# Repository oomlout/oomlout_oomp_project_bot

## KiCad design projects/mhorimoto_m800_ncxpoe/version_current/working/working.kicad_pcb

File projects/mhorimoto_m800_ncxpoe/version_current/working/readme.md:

# OOMP Project  
## M800-NCxPoE  by mhorimoto  
  
oomp key: oomp_projects_flat_mhorimoto_m800_ncxpoe  
(snippet of original readme)  
  
- NCxPoE  

  full source readme at [readme_src.md](readme_src.md)  
  
source repo at: [https://github.com/mhorimoto/M800-NCxPoE](https://github.com/mhorimoto/M800-NCxPoE)  
## Board  

## Schematic  

[schematic pdf](working_schematic.pdf)  
## Images

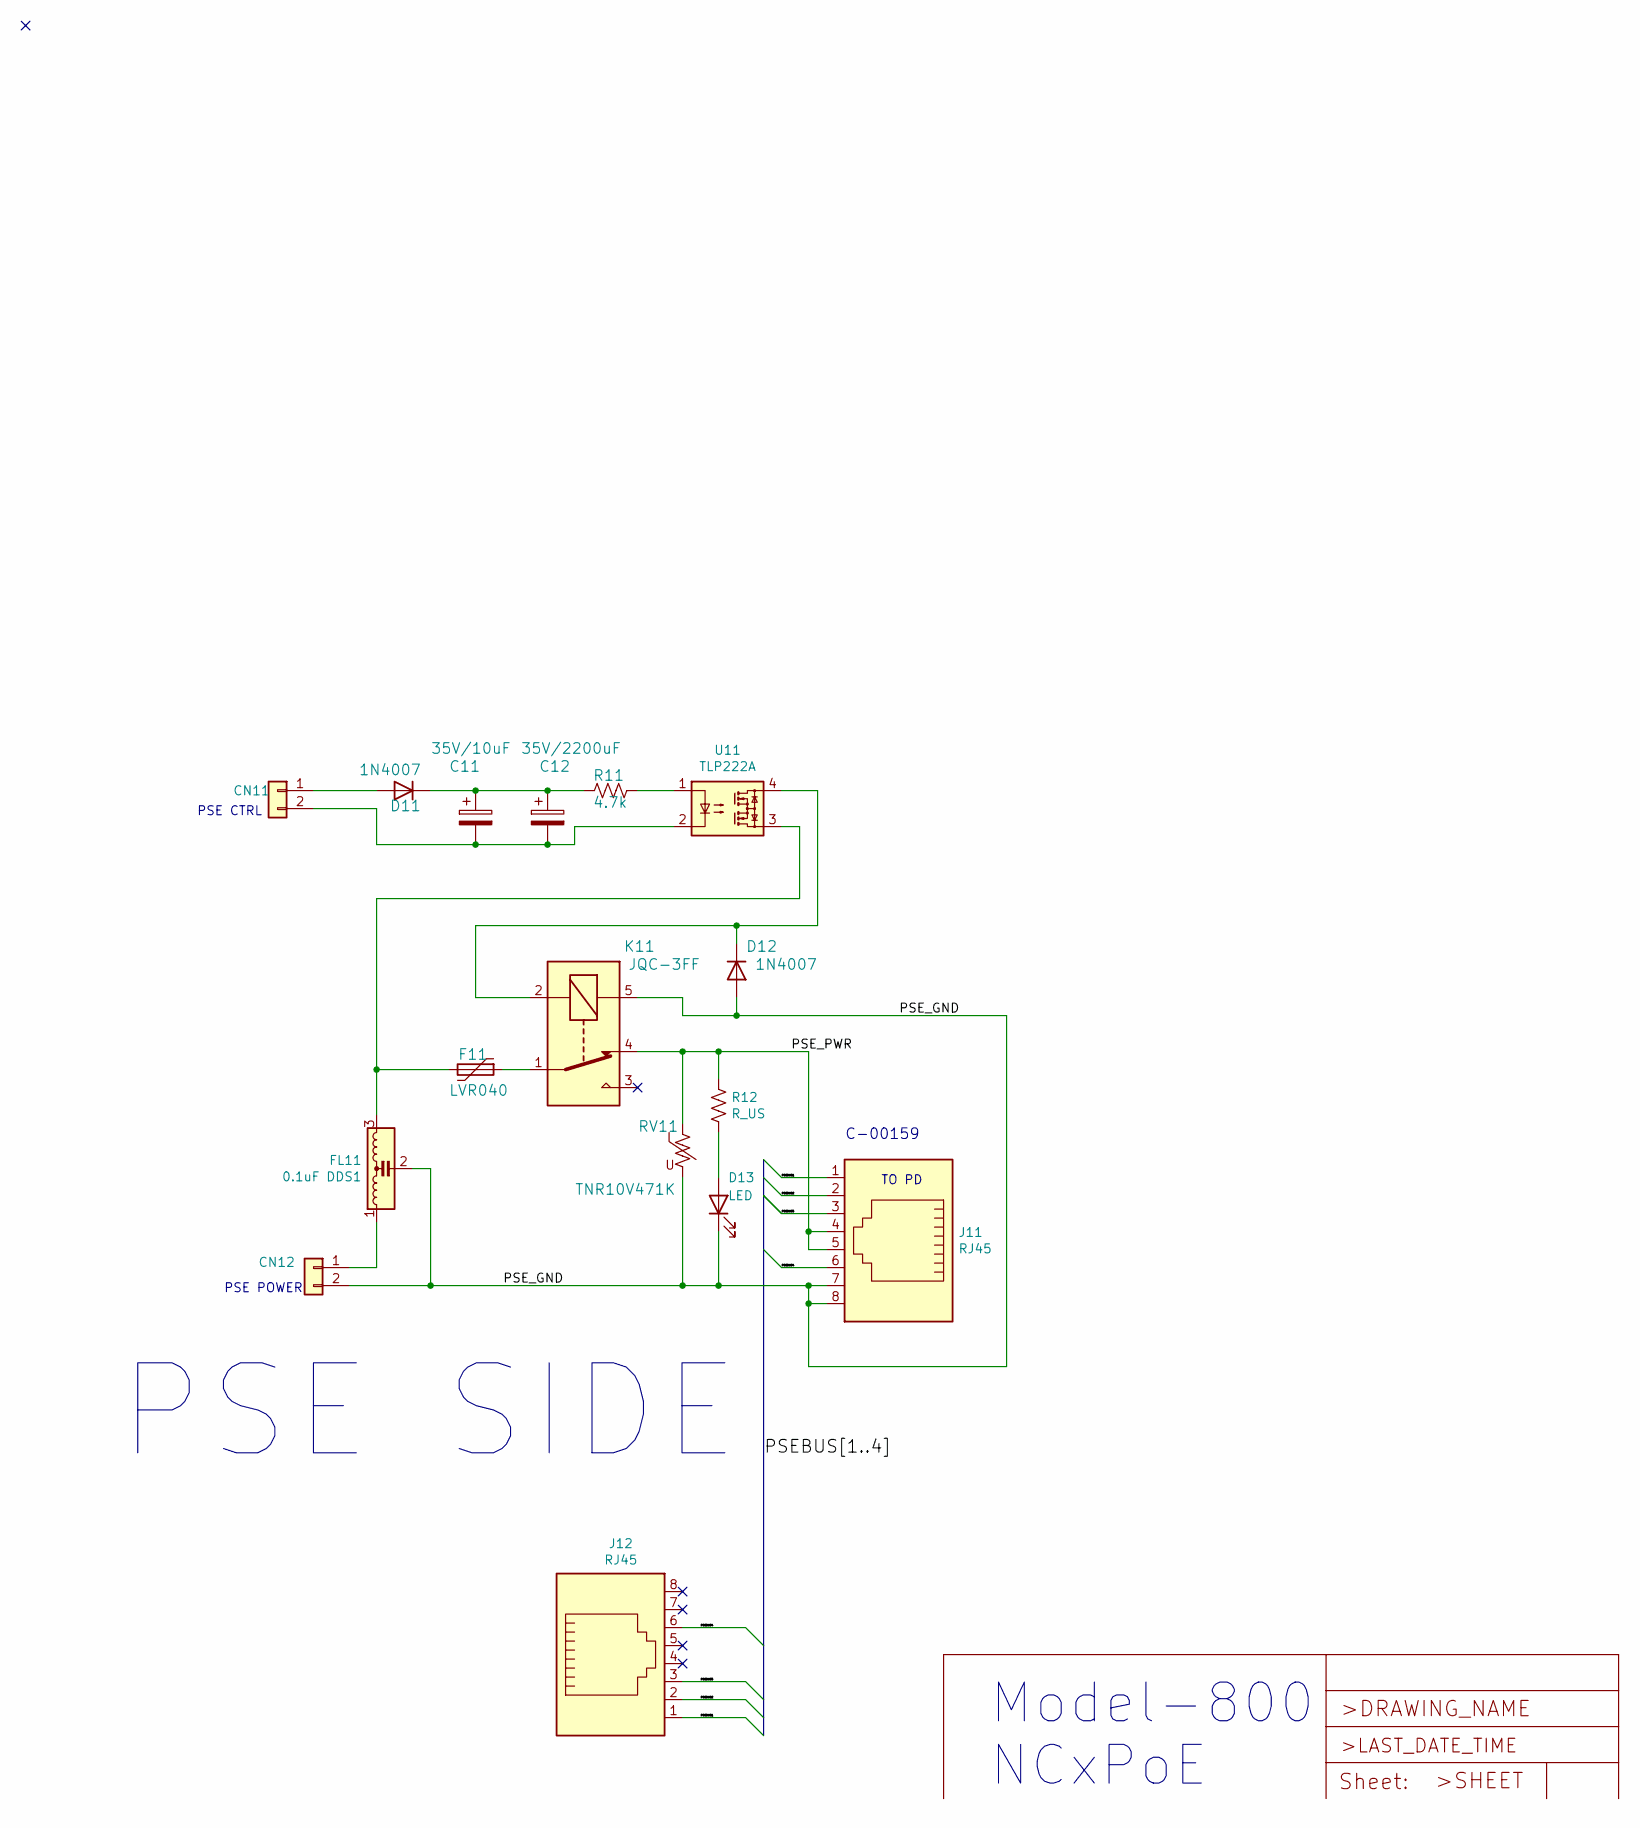
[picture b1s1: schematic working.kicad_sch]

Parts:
C11: 35V/10uF; C_Disc_D6.0mm_W2.5mm_P5.00mm
C12: 35V/2200uF; CP_Radial_D16.0mm_P7.50mm
CN11, CN12: 02-XH-A; JST_XH_B2B-XH-A_1x02_P2.50mm_Vertical
D11, D12: 1N4007; D_DO-41_SOD81_P10.16mm_Horizontal
D13: LED; LED_D3.0mm
F11: LVR040; Fuse_BelFuse_0ZRE0033FF_L11.4mm_W3.8mm
FL11: 0.1uF DDS1; DSS1
J11, J12: RJ45; RJ45_Neltron_7810-8P8C
K11: JQC-3FF; Relay_SPDT_Omron-G5LE-1
R11: 4.7k; R_Axial_DIN0207_L6.3mm_D2.5mm_P10.16mm_Horizontal
R12: R_US; R_Axial_DIN0207_L6.3mm_D2.5mm_P10.16mm_Horizontal
RV11: TNR10V471K; RV_Disc_D12mm_W3.9mm_P7.5mm
U11: TLP222A; DIP-4_W7.62mm

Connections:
/PSEBUS1: J11.1, J12.1
/PSEBUS2: J11.2, J12.2
/PSEBUS3: J11.3, J12.3
/PSEBUS4: J11.6, J12.6
/PSE_GND: CN12.2, D12.2 (A), D13.1 (K), FL11.2, J11.7, J11.8, K11.5, RV11.2
/PSE_PWR: J11.4, J11.5, K11.4, R12.1, RV11.1
unnamed: C11.1, C12.1, D11.1 (K), R11.2
unnamed: C11.2, C12.2, CN11.2, U11.2
unnamed: CN11.1, D11.2 (A)
unnamed: CN12.1, FL11.1
unnamed: D12.1 (K), K11.2, U11.4
unnamed: D13.2 (A), R12.2
unnamed: F11.1, K11.1
unnamed: F11.2, FL11.3, U11.3
unnamed: R11.1, U11.1

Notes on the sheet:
C-00159
PSE CTRL
TO PD
PSE POWER
PSE SIDE
Model-800 NCxPoE

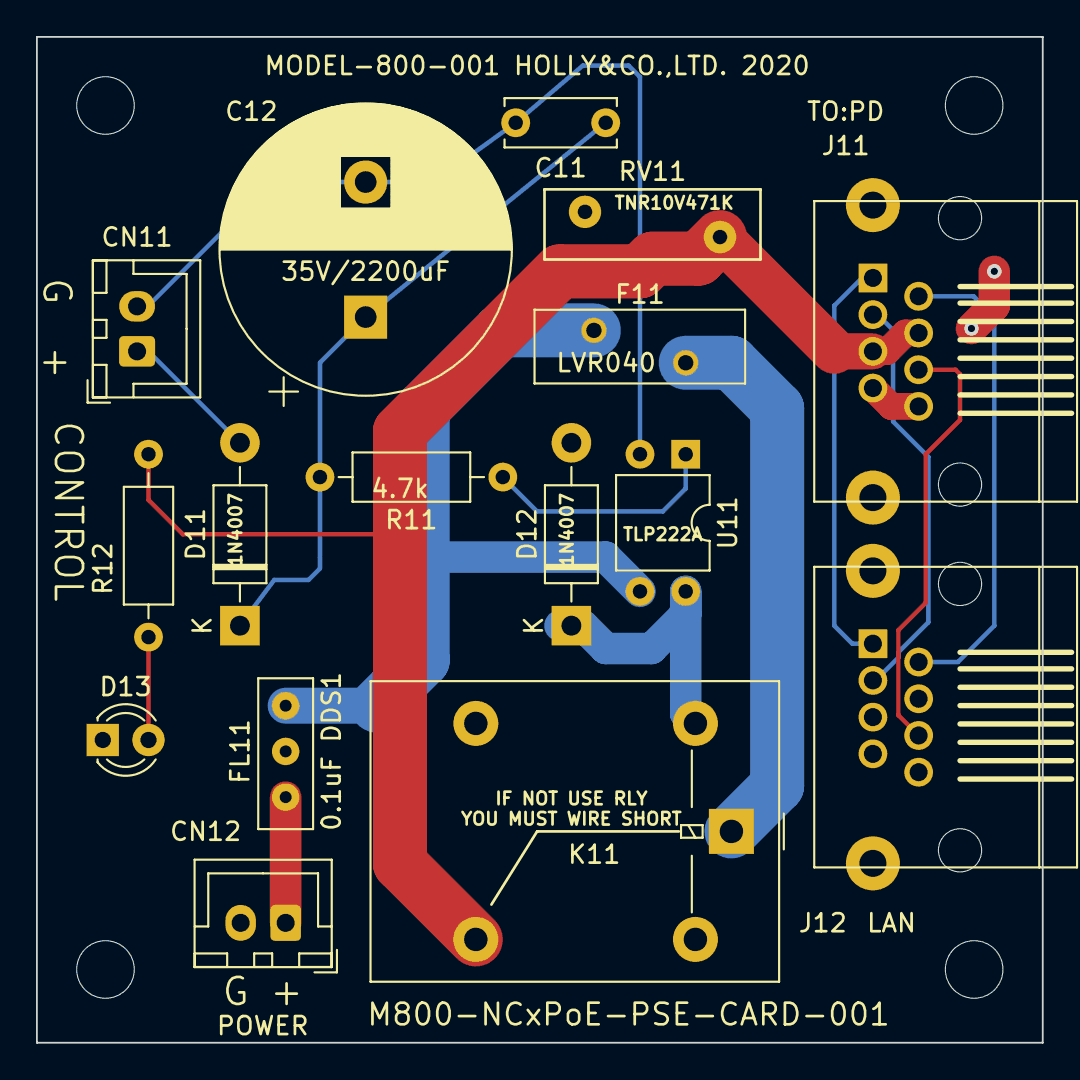
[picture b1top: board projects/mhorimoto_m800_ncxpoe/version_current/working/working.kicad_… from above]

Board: 2 copper layers, 55.9 x 55.9 mm, 16 parts (0 on the bottom side), 15 nets.

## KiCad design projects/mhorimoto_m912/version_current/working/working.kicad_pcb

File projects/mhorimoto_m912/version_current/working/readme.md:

# OOMP Project  
## M912  by mhorimoto  
  
oomp key: oomp_projects_flat_mhorimoto_m912  
(snippet of original readme)  
  
M912  
=====  
  
30th March 2021    
M.Horimoto  
  
-- 概要  
  
SOPi装置のフロントパネルに装着するLED用の基板。    
OPiなどの3.3Vの場合には510Ωから1kΩ程度の抵抗で良いと感じる。  
  
実装の向きなどは、3Dグラフィックを参照の上、組み立てる。  

なお、LEDが赤で表示されているが、色を特定するものではない。  
  
-- 部品  

| Item     | Model               | Spec          | PCS|  
|----------|---------------------|---------------|---:|  
| Base PCB | M912                |               |   1|  
| Registor | Carbon              | 500Ω〜1kΩ 1/6W | 3  |  
| LED      |                     | 3mmφ          |   3|  
| J1-Conn  | JST_XH_B4B-XH-A_1x04| JST-XH-A B4B  |   1|  

  full source readme at [readme_src.md](readme_src.md)  
  
source repo at: [https://github.com/mhorimoto/M912](https://github.com/mhorimoto/M912)  
## Board  

## Schematic  

[schematic pdf](working_schematic.pdf)  
## Images

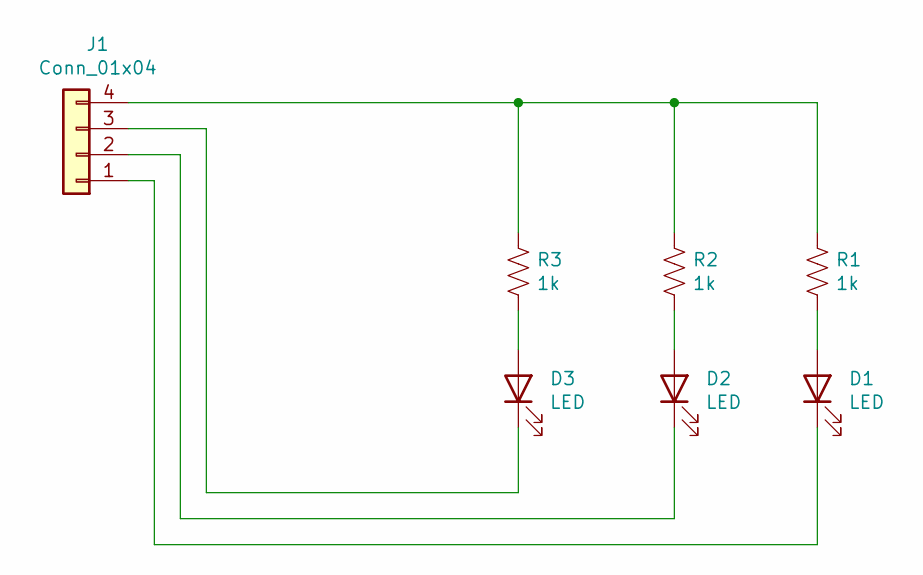
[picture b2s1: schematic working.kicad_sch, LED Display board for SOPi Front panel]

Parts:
D1, D2, D3: LED; LED_D3.0mm
J1: Conn_01x04; JST_XH_B4B-XH-A_1x04_P2.50mm_Vertical
R1, R2, R3: 1k; R_Axial_DIN0207_L6.3mm_D2.5mm_P7.62mm_Horizontal

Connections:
unnamed: D1.1 (K), J1.1
unnamed: D1.2 (A), R1.2
unnamed: D2.1 (K), J1.2
unnamed: D2.2 (A), R2.2
unnamed: D3.1 (K), J1.3
unnamed: D3.2 (A), R3.2
unnamed: J1.4, R1.1, R2.1, R3.1

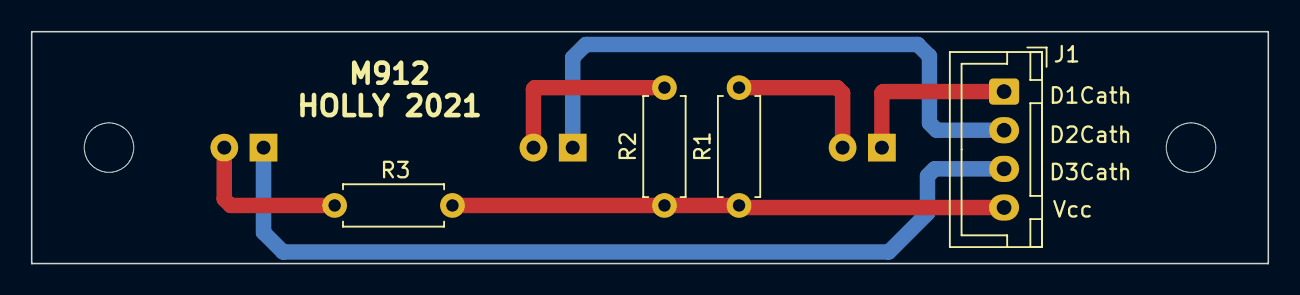
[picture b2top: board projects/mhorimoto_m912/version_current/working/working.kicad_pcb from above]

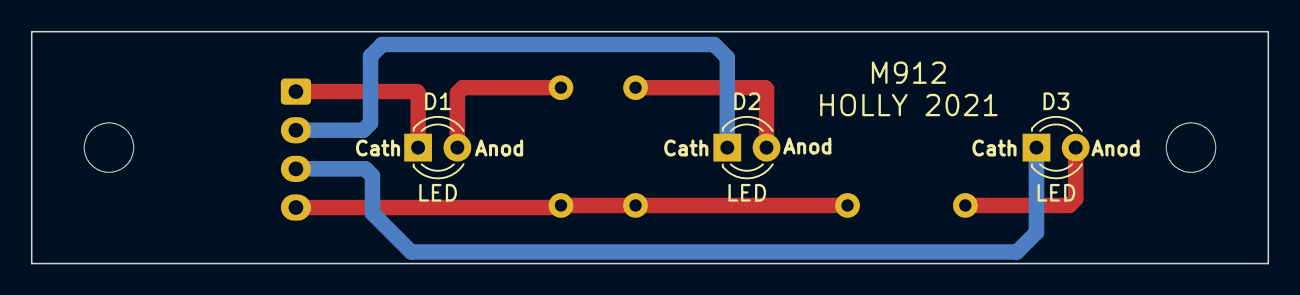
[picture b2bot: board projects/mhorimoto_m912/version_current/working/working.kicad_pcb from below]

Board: 2 copper layers, 80.0 x 15.0 mm, 7 parts (3 on the bottom side), 7 nets.

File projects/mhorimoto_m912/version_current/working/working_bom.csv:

"Id";"Designator";"Footprint";"Quantity";"Designation";"Supplier and ref";
1;"R3,R2,R1";"R_Axial_DIN0207_L6.3mm_D2.5mm_P7.62mm_Horizontal";3;"1k";;;
2;"J1";"JST_XH_B4B-XH-A_1x04_P2.50mm_Vertical";1;"Conn_01x04";;;
3;"D3,D2,D1";"LED_D3.0mm";3;"LED";;;

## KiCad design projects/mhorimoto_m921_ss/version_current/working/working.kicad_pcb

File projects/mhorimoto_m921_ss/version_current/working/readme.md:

# M921-SS by mhorimoto  
This is a harvested standardized copy of a project from github.  
The original project can be found at:  
https://github.com/mhorimoto/M921-SS  
Please consult that link for additional, details, files, and license information.  
Note: It was auto harvested and if the original repo had more than one board file or anything out of the ordinary the files here are likely not representative.

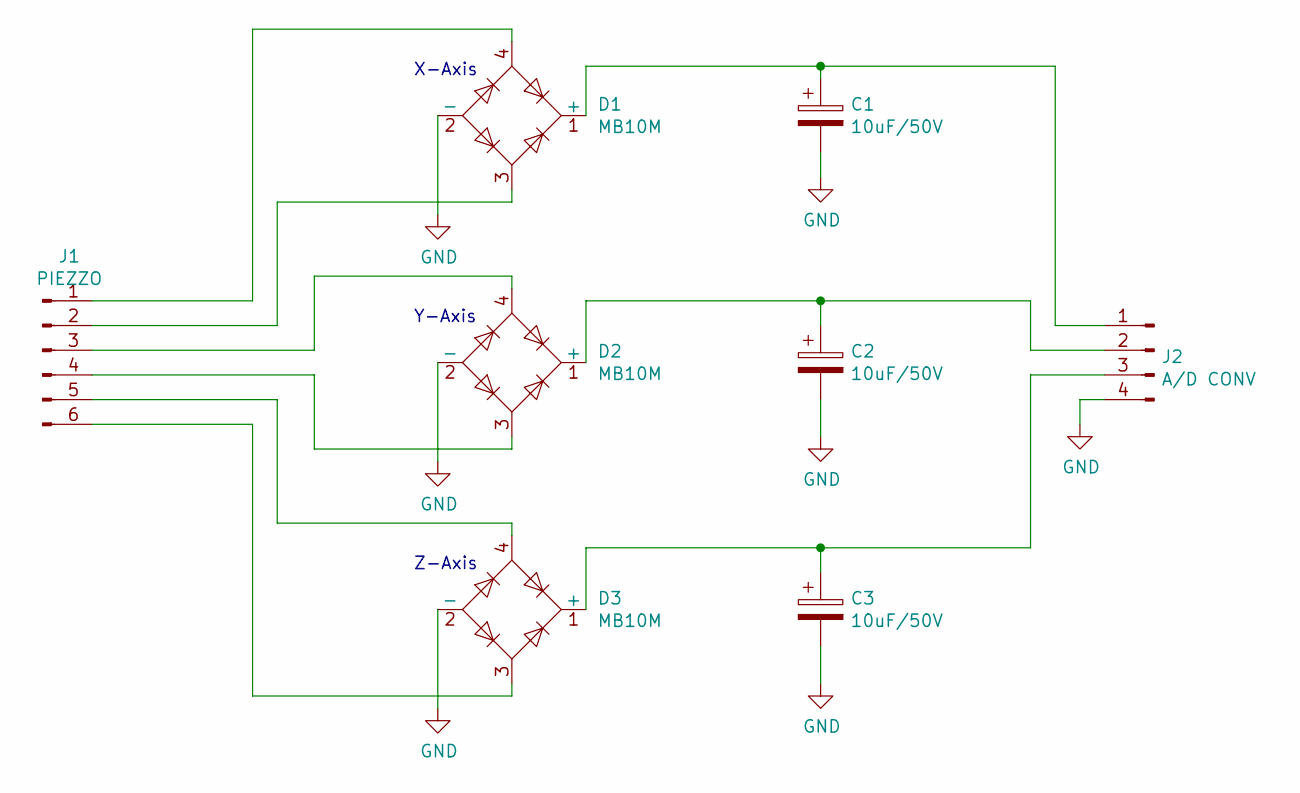
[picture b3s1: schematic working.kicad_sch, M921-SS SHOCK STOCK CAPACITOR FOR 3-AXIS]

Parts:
C1, C2, C3: 10uF/50V; CP_Radial_D5.0mm_P2.00mm
D1, D2, D3: MB10M
J1: PIEZZO; JST_XH_B6B-XH-A_1x06_P2.50mm_Vertical
J2: A/D CONV; JST_XH_B4B-XH-A_1x04_P2.50mm_Vertical

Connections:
GND: C1.2, C2.2, C3.2, D1.2 (-), D2.2 (-), D3.2 (-), J2.4
unnamed: C1.1, D1.1 (+), J2.1
unnamed: C2.1, D2.1 (+), J2.2
unnamed: C3.1, D3.1 (+), J2.3
unnamed: D1.3, J1.2
unnamed: D1.4, J1.1
unnamed: D2.3, J1.4
unnamed: D2.4, J1.3
unnamed: D3.3, J1.6
unnamed: D3.4, J1.5

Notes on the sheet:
Z-Axis
Y-Axis
X-Axis

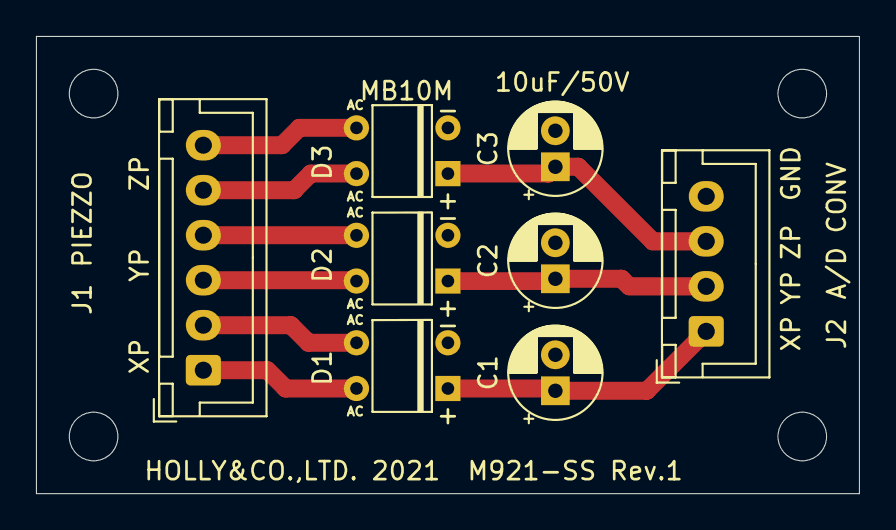
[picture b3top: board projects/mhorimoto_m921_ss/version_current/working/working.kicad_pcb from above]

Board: 2 copper layers, 45.7 x 25.4 mm, 8 parts (0 on the bottom side), 10 nets.

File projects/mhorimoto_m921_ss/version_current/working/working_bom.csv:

"Id";"Designator";"Footprint";"Quantity";"Designation";"Supplier and ref";
1;"J2";"JST_XH_B4B-XH-A_1x04_P2.50mm_Vertical";1;"A/D CONV";;;
2;"J1";"JST_XH_B6B-XH-A_1x06_P2.50mm_Vertical";1;"PIEZZO";;;
3;"D3,D2,D1";"MB10M";3;"MB10M";;;
4;"C3,C2,C1";"CP_Radial_D5.0mm_P2.00mm";3;"10uF/50V";;;

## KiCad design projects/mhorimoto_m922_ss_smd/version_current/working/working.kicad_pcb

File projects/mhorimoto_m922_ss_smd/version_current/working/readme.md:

# M922-SS-SMD by mhorimoto  
This is a harvested standardized copy of a project from github.  
The original project can be found at:  
https://github.com/mhorimoto/M922-SS-SMD  
Please consult that link for additional, details, files, and license information.  
Note: It was auto harvested and if the original repo had more than one board file or anything out of the ordinary the files here are likely not representative.

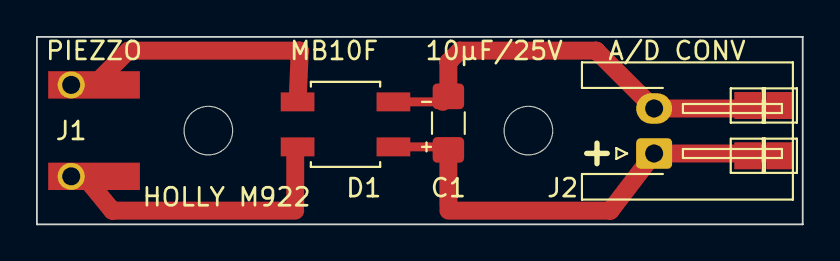
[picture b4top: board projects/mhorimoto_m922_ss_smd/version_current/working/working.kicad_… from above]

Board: 2 copper layers, 42.5 x 10.4 mm, 5 parts (0 on the bottom side), 4 nets.

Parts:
C1: 10μF/25V; C_1206_3216Metric_Pad1.42x1.75mm_HandSolder
D1: MB10F; DIOB_MB10F-13
J1: PIEZZO; LDT0-028K_MID
J2: A/D CONV; JST_XH_S2B-XH-A-1_1x02_P2.50mm_Horizontal
TP1: TestPoint_Pad_1.5x1.5mm

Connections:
unnamed: C1.1, D1.1, J2.1, TP1.1
unnamed: C1.2, D1.3, J2.2
unnamed: D1.2, J1.2
unnamed: D1.4, J1.1

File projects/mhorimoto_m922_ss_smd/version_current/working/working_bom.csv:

"Id";"Designator";"Footprint";"Quantity";"Designation";"Supplier and ref";
1;"C1";"C_1206_3216Metric_Pad1.42x1.75mm_HandSolder";1;"10μF/25V";;;
2;"D1";"DIOB_MB10F-13";1;"MB10F";;;
3;"J1";"LDT0-028K_MID";1;"PIEZZO";;;
4;"J2";"JST_XH_S2B-XH-A-1_1x02_P2.50mm_Horizontal";1;"A/D CONV";;;
5;",,";"";3;"";;;

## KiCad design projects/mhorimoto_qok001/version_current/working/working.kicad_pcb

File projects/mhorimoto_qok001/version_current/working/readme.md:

# qok001 by mhorimoto  
This is a harvested standardized copy of a project from github.  
The original project can be found at:  
https://github.com/mhorimoto/qok001  
Please consult that link for additional, details, files, and license information.  
Note: It was auto harvested and if the original repo had more than one board file or anything out of the ordinary the files here are likely not representative.

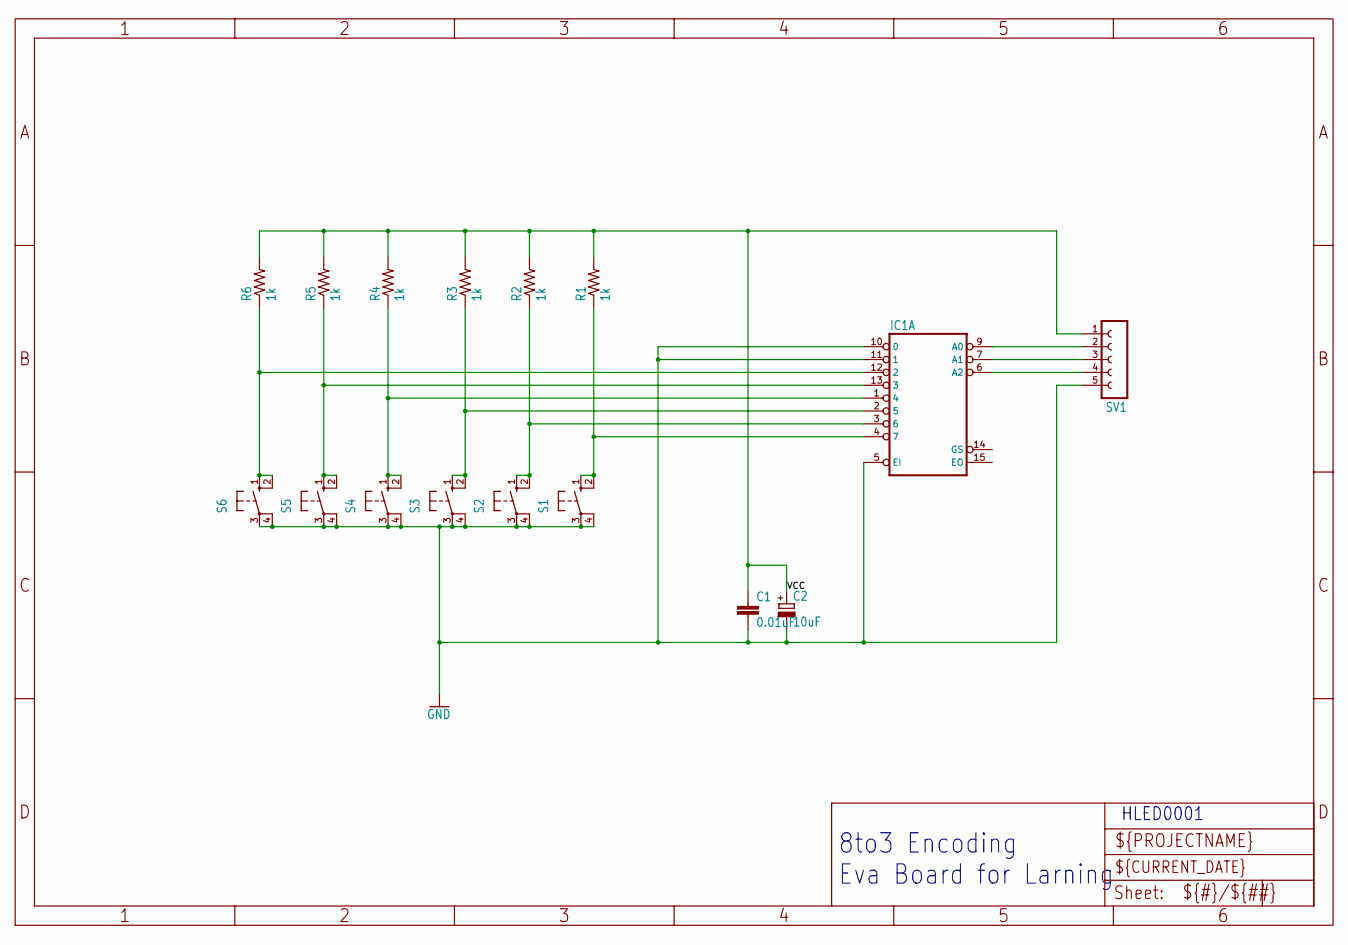
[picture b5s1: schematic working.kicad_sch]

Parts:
C1: 0.01uF; C025-025X050
C2: 10uF; E2,5-6E
IC1: 74148N; DIL16
R1, R2, R3, R4, R5, R6: 1k; 0207_7
S1, S2, S3, S4, S5, S6: 10-XX; B3F-10XX
SV1: FE05-1

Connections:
GND: C1.2, C2.-, IC1.5 (EI), IC1.8 (GND), IC1.10 (0), IC1.11 (1), S1.3, S1.4 (P1), S2.3, S2.4 (P1), S3.3, S3.4 (P1), S4.3, S4.4 (P1), S5.3, S5.4 (P1), S6.3, S6.4 (P1), SV1.5
unnamed: IC1.4 (7), R1.1, S1.1 (S), S1.2 (S1)
unnamed: IC1.3 (6), R2.1, S2.1 (S), S2.2 (S1)
unnamed: IC1.2 (5), R3.1, S3.1 (S), S3.2 (S1)
unnamed: IC1.1 (4), R4.1, S4.1 (S), S4.2 (S1)
unnamed: IC1.13 (3), R5.1, S5.1 (S), S5.2 (S1)
unnamed: IC1.12 (2), R6.1, S6.1 (S), S6.2 (S1)
unnamed: IC1.9 (A0), SV1.2
unnamed: IC1.7 (A1), SV1.3
unnamed: IC1.6 (A2), SV1.4
VCC: C1.1, C2.+, IC1.16 (VCC), R1.2, R2.2, R3.2, R4.2, R5.2, R6.2, SV1.1

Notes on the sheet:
8to3 Encoding Eva Board for Larning
HLED0001

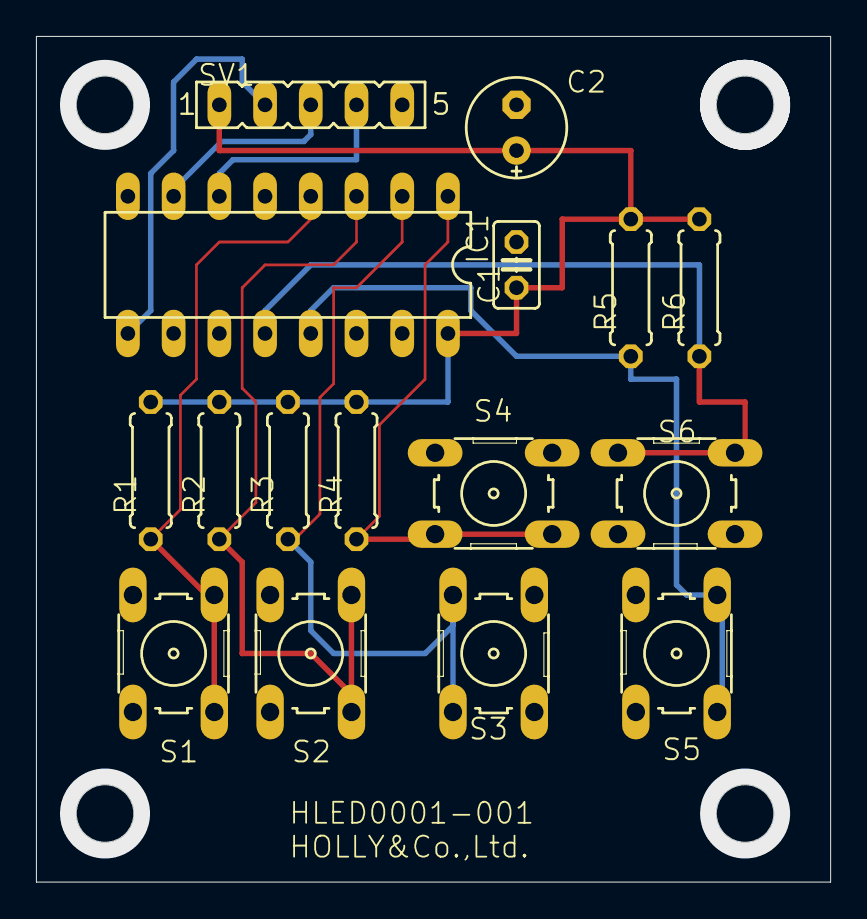
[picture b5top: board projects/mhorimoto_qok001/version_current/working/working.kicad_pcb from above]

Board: 2 copper layers, 44.1 x 47.0 mm, 20 parts (0 on the bottom side), 11 nets.

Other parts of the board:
@HOLE0, @HOLE1, @HOLE2, @HOLE3: (no value)

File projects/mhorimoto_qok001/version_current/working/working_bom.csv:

"Id";"Designator";"Footprint";"Quantity";"Designation";"Supplier and ref";
1;"S3,S5,S2,S6,S1,S4";"B3F-10XX";6;"";;;
2;"R2,R6,R4,R5,R3,R1";"0207_7";6;"1k";;;
3;"@HOLE0,@HOLE1,@HOLE3,@HOLE2";"";4;"";;;
4;"C1";"C025-025X050";1;"0.01uF";;;
5;"SV1";"FE05-1";1;"";;;
6;"C2";"E2,5-6E";1;"10uF";;;
7;"IC1";"DIL16";1;"74HC148N";;;

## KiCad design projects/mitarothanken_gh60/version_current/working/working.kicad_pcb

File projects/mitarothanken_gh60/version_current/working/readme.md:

# OOMP Project  
## gh60  by mitaroThanken  
  
oomp key: oomp_projects_flat_mitarothanken_gh60  
(snippet of original readme)  

  full source readme at [readme_src.md](readme_src.md)  
  
source repo at: [https://github.com/mitaroThanken/gh60](https://github.com/mitaroThanken/gh60)  
## Board  

## Schematic  

[schematic pdf](working_schematic.pdf)  
## Images

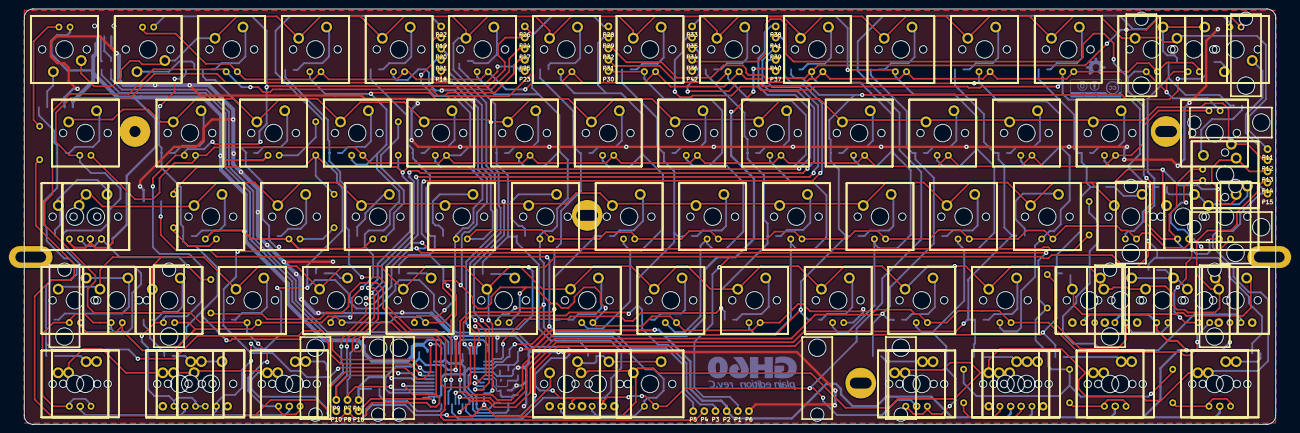
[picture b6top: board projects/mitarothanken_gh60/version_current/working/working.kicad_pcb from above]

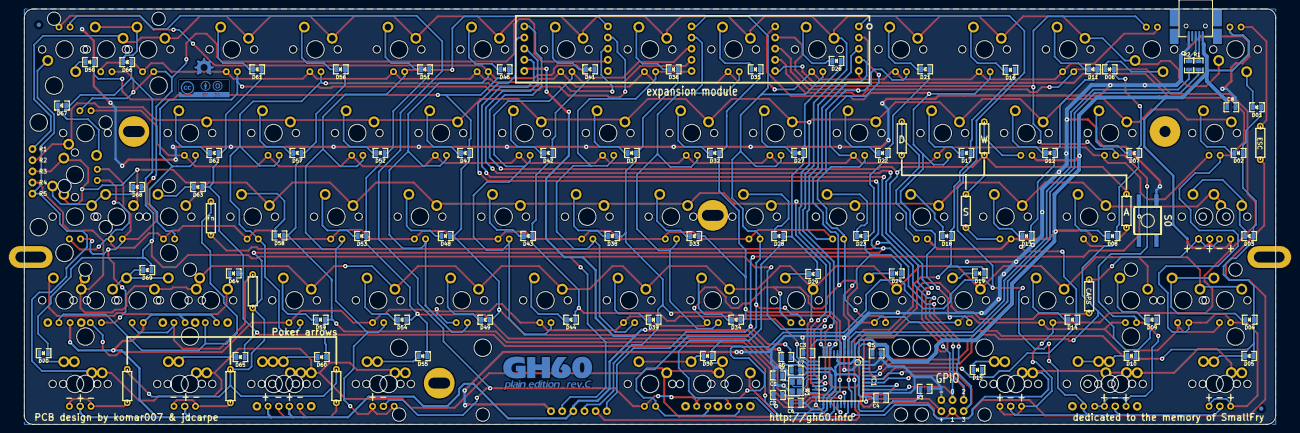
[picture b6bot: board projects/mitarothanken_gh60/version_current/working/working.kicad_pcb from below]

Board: 2 copper layers, 285.0 x 94.6 mm, 335 parts (94 on the bottom side), 130 nets.

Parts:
C1, C2: 22p; 0805C
C3, C8: 1u; 0805C
C4, C5, C6, C7: 100n; 0805C
D01, D02, D03, D04, D05, D06, D07, D08, D09, D10, D11, D12, D13, D14, D15, D16, D17, D18, D19, D21, D22, D23, D24, D26, D27, D28, D29, D30, D31, D32, D33, D34, D36, D37, D38, D39, D41, D42, D43, D44, D46, D47, D48, D49, D50, D51, D52, D53, D54, D55, D56, D57, D58, D59, D60, D61, D62, D63, D64, D65, D66, D67, D68, D69, D70: 1N4148; 0805D
DB02, DB04, DB06, DB07, DB09, DB11, DB14, DB16, DB17, DB19, DB21, DB22, DB23, DB24, DB26, DB27, DB28, DB29, DB30, DB31, DB32, DB33, DB34, DB36, DB37, DB38, DB39, DB041, DB41, DB42, DB43, DB44, DB46, DB47, DB48, DB49, DB50, DB51, DB52, DB53, DB54, DB56, DB57, DB58, DB59, DB61, DB62, DB63, DB66, DB67, DB68, DB69, DB301, DB302, DB661, DB681, DB682: LED; MX1A-led_no3d
DB05, DB10, DB15, DB051, DB55, DB101, DB102, DB151, DB551: LED; MX1A-led
DC1, DC2: LED; MX1A-led_no3d
DC3: LED; MX1A-led
DF3, DF10, DF11, DF20, DF201: LED; MX1A-led_no3d
DF21, DF22, DF23, DF211, DF221, DF231, DF232: LED; MX1A-led
DW1, DW2, DW3, DW4: LED; MX1A-led_no3d
FID: FIDUCIAL
FID#2: FIDUCIAL
HOLE: VAL**; PKRHSL
HOLE#2: VAL**; PKRHSL
HOLE#3, HOLE#4, HOLE#5: VAL**; PKRH
HOLE#6: VAL**; PKRHC
IC1: ATMEGA32U4; TQFP44
J1: MINI; 67503
MXST: VAL**; MXST
MXST#2, MXST#3, MXST#4, MXST#5, MXST#6, MXST#7, MXST#8, MXST#9, MXST#10, MXST#11, MXST#12, MXST#13, MXST#14, MXST#15: VAL**; MXST
MXWIRE: VAL**; MX1A-wire
MXWIRE#2, MXWIRE#3, MXWIRE#4, MXWIRE#5, MXWIRE#6, MXWIRE#7, MXWIRE#8, MXWIRE#9: VAL**; MX1A-wire
P1, P2, P3, P4, P5, P6, P7, P8, P9, P10, P11, P12, P13, P14, P15, P16, P17, P18, P19, P20, P21, P22, P23, P24, P25, P26, P27, P28, P29, P30, P31, P32, P33, P34, P35, P36, P37, P38, P39, P40, P41, P42: CONN_1; pad
R1, R2: 22; 0805R
R3, R5: 10k; 0805R
R4: 300; resistor
R6, R7, R8, R9, R10, R11, R12, R13, R14, R15: R; resistor
S0: DTSM-6; KSEM31GLFS
S01, S02, S03, S04, S05, S06, S07, S08, S10, S11, S12, S13, S14, S15, S16, S17, S18, S19, S21, S22, S23, S24, S26, S27, S28, S29, S30, S31, S32, S33, S34, S36, S37, S38, S39, S41, S42, S43, S44, S46, S47, S48, S49, S51, S52, S53, S54, S55, S56, S57, S58, S59, S60, S61, S62, S65, S66, S67, S68, S69, S70: MX1A
S09, S031, S041, S50, S63, S64, S101, S102, S151, S301, S302, S0512, S552, S601, S602, S641, S661, S681, S682, S691, S692, S6512, S7012: MX1A; MX1A_no3d
X1: ASX3F; 4-SMD

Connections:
/GPIO0: IC1.36, P7.1, P38.1, R6.1, R7.1, R8.1, R9.1
/GPIO1: IC1.37, P8.1, P39.1, R12.1
/GPIO2: IC1.38, P9.1, P40.1, R10.1
/GPIO3: IC1.39, P10.1, P41.1, R11.1, R13.1, R14.1, R15.1
/Leds/lcol1: DB02.1, DB04.1, DB05.1, DB041.1, DB051.1, P23.1
/Leds/lcol2: DB06.1, DB07.1, DB09.1, DB10.1, DB101.1, DB102.1, P24.1
/Leds/lcol3: DB11.1, DB14.1, DB15.1, DB151.1, P25.1
/Leds/lcol4: DB16.1, DB17.1, DB19.1, P26.1
/Leds/lcol5: DB21.1, DB22.1, DB23.1, DB24.1, P27.1
/Leds/lcol6: DB26.1, DB27.1, DB28.1, DB29.1, DB30.1, DB301.1, DB302.1, P28.1
/Leds/lcol7: DB31.1, DB32.1, DB33.1, DB34.1, P29.1
/Leds/lcol8: DB36.1, DB37.1, DB38.1, DB39.1, P30.1
/Leds/lcol9: DB41.1, DB42.1, DB43.1, DB44.1, P31.1
/Leds/lcol10: DB46.1, DB47.1, DB48.1, DB49.1, DB50.1, P32.1
/Leds/lcol11: DB51.1, DB52.1, DB53.1, DB54.1, DB55.1, DB551.1, P33.1
/Leds/lcol12: DB56.1, DB57.1, DB58.1, DB59.1, P34.1
/Leds/lcol13: DB61.1, DB62.1, DB63.1, P35.1
/Leds/lcol14: DB66.1, DB67.1, DB68.1, DB69.1, DB661.1, DB681.1, DB682.1, P36.1
/Leds/lrow1: DB06.2, DB11.2, DB16.2, DB21.2, DB26.2, DB31.2, DB36.2, DB41.2, DB46.2, DB51.2, DB56.2, DB61.2, DB66.2, DB661.2, P18.1
/Leds/lrow2: DB02.2, DB07.2, DB17.2, DB22.2, DB27.2, DB32.2, DB37.2, DB42.2, DB47.2, DB52.2, DB57.2, DB62.2, DB67.2, P19.1
/Leds/lrow3: DB23.2, DB28.2, DB33.2, DB38.2, DB43.2, DB48.2, DB53.2, DB58.2, DB63.2, DB68.2, DB681.2, DB682.2, P20.1
/Leds/lrow4: DB04.2, DB09.2, DB14.2, DB19.2, DB24.2, DB29.2, DB34.2, DB39.2, DB041.2, DB44.2, DB49.2, DB54.2, DB59.2, DB69.2, P21.1
/Leds/lrow5: DB05.2, DB10.2, DB15.2, DB30.2, DB50.2, DB051.2, DB55.2, DB101.2, DB102.2, DB151.2, DB301.2, DB302.2, DB551.2, P22.1
/MISO: D66.1, D67.1, D68.1, D69.1, D70.1, IC1.11, P1.1
/MOSI: IC1.10, P4.1, R4.2
/SCK: D36.1, D37.1, D38.1, D39.1, IC1.9, P3.1
/col1: D01.1, D02.1, D03.1, D04.1, D05.1, IC1.41
/col2: D06.1, D07.1, D08.1, D09.1, D10.1, IC1.40
/col3: D11.1, D12.1, D13.1, D14.1, D15.1, IC1.1
/col4: D16.1, D17.1, D18.1, D19.1, IC1.32
/col5: D21.1, D22.1, D23.1, D24.1, IC1.31
/col6: D26.1, D27.1, D28.1, D29.1, D30.1, IC1.30
/col7: D31.1, D32.1, D33.1, D34.1, IC1.25
/col9: D41.1, D42.1, D43.1, D44.1, IC1.12
/col10: D46.1, D47.1, D48.1, D49.1, D50.1, IC1.29
/col11: D51.1, D52.1, D53.1, D54.1, D55.1, IC1.28
/col12: D56.1, D57.1, D58.1, D59.1, D60.1, IC1.27
/col13: D61.1, D62.1, D63.1, D64.1, D65.1, IC1.26
/row1: IC1.18, P11.1, S01.1, S06.1, S11.1, S16.1, S21.1, S26.1, S31.1, S36.1, S41.1, S46.1, S51.1, S56.1, S61.1, S66.1, S661.1
/row2: IC1.19, P12.1, S02.1, S07.1, S12.1, S17.1, S22.1, S27.1, S32.1, S37.1, S42.1, S47.1, S52.1, S57.1, S62.1, S67.1
/row3: IC1.20, P13.1, S03.1, S08.1, S13.1, S18.1, S23.1, S28.1, S031.2, S33.1, S38.1, S43.1, S48.1, S53.1, S58.1, S63.1, S68.1, S681.1, S682.2
/row4: IC1.21, P14.1, S04.1, S09.1, S14.1, S19.1, S24.1, S29.1, S34.1, S39.1, S041.1, S44.1, S49.1, S54.1, S59.1, S64.2, S69.1, S641.1, S691.2, S692.1
/row5: IC1.22, P15.1, S05.1, S10.1, S15.1, S30.1, S50.1, S55.1, S60.1, S65.1, S70.1, S101.1, S102.1, S151.1, S301.1, S302.1, S0512.1, S552.1, S601.1, S602.1, S6512.1, S7012.1
/~RES~: IC1.13, P5.1, R5.2, S0.3
GND: C1.2, C2.2, C3.2, C4.2, C5.2, C6.2, C7.2, C8.2, IC1.5, IC1.15, IC1.23, IC1.35, IC1.43, J1.5, P6.1, P17.1, P42.1, R3.2, S0.1, X1.2, X1.4
unnamed: C1.1, IC1.16, X1.1
unnamed: C2.1, IC1.17, X1.3
unnamed: C3.1, IC1.6
unnamed: D01.2, S01.2
unnamed: D02.2, S02.2
unnamed: D03.2, S03.2, S031.1
unnamed: D04.2, S04.2, S041.2
unnamed: D05.2, S05.2, S0512.2
unnamed: D06.2, S06.2
unnamed: D07.2, S07.2
unnamed: D08.2, S08.2
unnamed: D09.2, S09.2
unnamed: D10.2, S10.2, S101.2, S102.2
unnamed: D11.2, S11.2
unnamed: D12.2, S12.2
unnamed: D13.2, S13.2
unnamed: D14.2, S14.2
unnamed: D15.2, S15.2, S151.2
unnamed: D16.2, S16.2
unnamed: D17.2, S17.2
unnamed: D18.2, S18.2
unnamed: D19.2, S19.2
unnamed: D21.2, S21.2
unnamed: D22.2, S22.2
unnamed: D23.2, S23.2
unnamed: D24.2, S24.2
unnamed: D26.2, S26.2
unnamed: D27.2, S27.2
unnamed: D28.2, S28.2
unnamed: D29.2, S29.2
unnamed: D30.2, S30.2, S301.2, S302.2
unnamed: D31.2, S31.2
unnamed: D32.2, S32.2
unnamed: D33.2, S33.2
unnamed: D34.2, S34.2
unnamed: D36.2, S36.2
unnamed: D37.2, S37.2
unnamed: D38.2, S38.2
unnamed: D39.2, S39.2
unnamed: D41.2, S41.2
unnamed: D42.2, S42.2
unnamed: D43.2, S43.2
unnamed: D44.2, S44.2
unnamed: D46.2, S46.2
unnamed: D47.2, S47.2
unnamed: D48.2, S48.2
unnamed: D49.2, S49.2
unnamed: D50.2, S50.2
unnamed: D51.2, S51.2
unnamed: D52.2, S52.2
unnamed: D53.2, S53.2
unnamed: D54.2, S54.2
unnamed: D55.2, S55.2, S552.2
unnamed: D56.2, S56.2
unnamed: D57.2, S57.2
unnamed: D58.2, S58.2
unnamed: D59.2, S59.2
unnamed: D60.2, S60.2, S601.2, S602.2
unnamed: D61.2, S61.2
unnamed: D62.2, S62.2
unnamed: D63.2, S63.2
unnamed: D64.2, S64.1, S641.2
unnamed: D65.2, S65.2, S6512.2
unnamed: D66.2, S66.2, S661.2
unnamed: D67.2, S67.2
unnamed: D68.2, S68.2, S681.2, S682.1
unnamed: D69.2, S69.2, S691.1, S692.2
unnamed: D70.2, S70.2, S7012.2
unnamed: DC1.2, DC2.2, DC3.2, R4.1
unnamed: DF3.2, R12.2
unnamed: DF10.2, DF11.2, R10.2
unnamed: DF20.2, DF201.2, R11.2
unnamed: DF21.2, DF211.2, R13.2
unnamed: DF22.2, DF221.2, R14.2
unnamed: DF23.2, DF231.2, DF232.2, R15.2
unnamed: DW1.2, R6.2
unnamed: DW2.2, R7.2
unnamed: DW3.2, R8.2
unnamed: DW4.2, R9.2
unnamed: IC1.3, R1.1
unnamed: IC1.4, R2.1
unnamed: IC1.33, R3.1
unnamed: J1.2, R1.2
unnamed: J1.3, R2.2
VCC: C4.1, C5.1, C6.1, C7.1, C8.1, DC1.1, DC2.1, DC3.1, DF3.1, DF10.1, DF11.1, DF20.1, DF21.1, DF22.1, DF23.1, DF201.1, DF211.1, DF221.1, DF231.1, DF232.1, DW1.1, DW2.1, DW3.1, DW4.1, IC1.2, IC1.7, IC1.14, IC1.24, IC1.34, IC1.44, J1.1, P2.1, P16.1, P37.1, R5.1

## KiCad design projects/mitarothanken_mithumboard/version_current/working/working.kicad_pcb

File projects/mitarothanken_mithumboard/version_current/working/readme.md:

# OOMP Project  
## mithumboard  by mitaroThanken  
  
oomp key: oomp_projects_flat_mitarothanken_mithumboard  
(snippet of original readme)  
  
- mithumboard  
  
市販のキーボードに追加して、親指が活用できるようにする、つもり。WIP。  
  
  full source readme at [readme_src.md](readme_src.md)  
  
source repo at: [https://github.com/mitaroThanken/mithumboard](https://github.com/mitaroThanken/mithumboard)  
## Board  

## Schematic  

[schematic pdf](working_schematic.pdf)  
## Images

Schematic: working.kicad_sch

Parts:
C1: 0.1u; C_0603_1608Metric_Pad1.05x0.95mm_HandSolder
C2: 47u/16V; CP_Elec_6.3x5.4_Nichicon
C3, C4: 1u; C_0603_1608Metric_Pad1.05x0.95mm_HandSolder
H1, H2, H3, H4: MountingHole; MountingHole_2.2mm_M2
J1, J2, J3, J4: MJ-4PP-9; MJ-4PP-9_1side
R1: 10k; R_0603_1608Metric_Pad1.05x0.95mm_HandSolder
SW1, SW2, SW3, SW4, SW5, SW6, SW7, SW8, SW9, SW10, SW11, SW12, SW13, SW14, SW15: SW_Push; CherryMX_Choc_Hotswap_1side
SW16: SW_DIP_x04; SW_DIP_SPSTx04_Slide_Copal_CHS-04B_W7.62mm_P1.27mm
U1: TCA9555PWR; TSSOP-24_4.4x7.8mm_P0.65mm

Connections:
A0: SW16.3, U1.21 (A0)
A1: SW16.2, U1.2 (A1)
A2: SW16.1, U1.3 (A2)
GND: C1.2, C2.2, C3.2, C4.2, J1.A, J2.A, SW1.1, SW2.1, SW3.1, SW4.1, SW5.1, SW6.1, SW7.1, SW8.2, SW9.2, SW10.1, SW11.1, SW12.1, SW13.2, SW14.2, SW15.2, SW16.5, SW16.6, SW16.7, SW16.8, U1.24 (VCC)
INT: J3.C, J4.C, R1.1, U1.1 (~INT)
R1C1: SW1.2, U1.15 (P12)
R1C2: SW4.2, U1.18 (P15)
R1C3: SW7.2, U1.4 (P00)
R1C4: SW10.2, U1.7 (P03)
R1C5: SW13.1, U1.8 (P04)
R2C1: SW2.2, U1.14 (P11)
R2C2: SW5.2, U1.17 (P14)
R2C3: SW8.1, U1.19 (P16)
R2C4: SW11.2, U1.6 (P02)
R2C5: SW14.1, U1.9 (P05)
R3C1: SW3.2, U1.13 (P10)
R3C2: SW6.2, U1.16 (P13)
R3C3: SW9.1, U1.20 (P17)
R3C4: SW12.2, U1.5 (P01)
R3C5: SW15.1, U1.10 (P06)
SCL: J1.C, J2.C, U1.22 (SCL)
SDA: J1.B, J2.B, U1.23 (SDA)
VCC: C1.1, C2.1, C3.1, C4.1, J1.D, J2.D, R1.2, U1.12 (GND)
